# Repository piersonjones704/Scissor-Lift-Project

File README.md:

# Scissor Lift Project 
## Preventing scissor lift collisions on construction sites

### Overview  
This project, developed in collaboration with **Skanska**, aims to reduce jobsite accidents by integrating a **low-cost collision detection and avoidance system** into industrial scissor lifts.  

---

### Team  
- **Team Members:** Pierson Jones, Parker Jones, Jack Oakman, Aaryan Nanekar 
- **Project Lead:** Pierson Jones
- **Mechatronics Team Lead:** Parker Jones 
- **Client Partner:** Skanska USA

---

### License  
This project is currently **private and under client collaboration**. Portions may be shared publicly for academic or demonstration purposes only.

---

### Acknowledgements  
Special thanks to **Skanska, Duke University’s EGR101 & EGR102 Course, Dr. Glass, and Shane Trent** for mentorship, technical guidance, and access to testing and prototyping facilities.

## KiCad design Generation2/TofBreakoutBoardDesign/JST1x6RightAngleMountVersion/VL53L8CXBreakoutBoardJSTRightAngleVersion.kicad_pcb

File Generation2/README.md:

# Scissor Lift Collision Prevention Module
## Generation 2 - Time of Flight Sensors

### Overview  
This project, developed in collaboration with **Skanska**, aims to reduce jobsite accidents by integrating a **low-cost collision detection and avoidance system** into industrial scissor lifts.  

Generation 2 is a work in progress. The goal is to replace Generation 1's single mechanically-swept ultrasonic module with a static array of  6 VL53L8CX time-of-flight sensors, each mounted at a different fixed angle around the lift — eliminating the need for a servo sweep entirely. 

This semester, single-sensor operation was validated end-to-end, including adaptive ranging and a power-optimized configuration. Reliably running all 6 sensors on a shared I2C bus has been achieved. To complete this generation, combining all 6 sensors, with the buzzer and hysteresis logic, is next.

---

### Key Features  
**Validated (single sensor):**
- **2 Axes of Detection:** 6 VL53L8CX time of flight sensor readings for reliable distance measurement under varying noise and lighting conditions for 90° vertical and 135° horizontal per module.
- **Adaptive Ranging:** Frequency scales between **1 Hz (idle/far range)** and **6 Hz (near-range detection)** based on the closest detected object, with hysteresis (2 consecutive near readings to speed up; object gone 4+ seconds and 2 consecutive far readings to slow back down). Resolution held fixed at 4×4 to avoid the heavier reconfiguration cost of a resolution switch.
- **Smoothed Buzzer Alerts:** Proximity-based beep profiles that step one level at a time rather than jumping directly to a target profile.
- **Structured Power Optimization:** Configuration changes (ranging frequency, resolution, integration time, ranging mode, ESP32 light sleep with INT-pin wake, VHV recalibration interval) were tested one variable at a time (Tests 1–17) against a shared baseline, with current logged at each step to guide the final single-sensor configuration. Key findings: autonomous mode draws short bursts (~42–45 mA at 8×8, ~16 mA at 4×4) versus a sustained ~66 mA in continuous mode, and ESP32 light sleep reduced system draw from ~50 mA to ~11 mA (USB attached, like-for-like). In a 30-minute bench-supply comparison (no USB, 20% object-detected weighting), the estimated 10-hour energy use of the single-sensor module fell from ~480 mAh (baseline) to ~19 mAh (optimized), a ~96% reduction. Limitations: sub-milliamp averages were calculated from duty cycle rather than measured directly because multimeter sampling cannot resolve short bursts; the baseline was measured on USB power and the optimized run on a bench supply; and Wi-Fi and hardware-shutdown (LPn) power effects were not tested. Full 6-sensor array power has not yet been characterized.

**Validated (multi-sensor, in progress toward full 6-sensor array):**
- **Multi-Sensor I2C Addressing:** Multi-Sensor I2C Addressing: A hardware I2C multiplexer (TCA9548A/PCA9548A) successfully addresses all 6 VL53L8CX sensors simultaneously, each mounted at its intended final angle. Channel-to-angle mapping (each sensor's mountYawDeg/mountPitchDeg in firmware) has been verified against physical sensor position, not just assumed. An earlier unreliable version of multi-sensor addressing was root-caused to an intermittent short between adjacent breadboard pull-up resistor leads. This was not an addressing or firmware issue. Additionally, it is important to note that channel 4 on the MUX is not working and consistently causes channel 3 and onwards to fail. Thus, sensor 5 is being put on channel 5. A separate software-assigned addressing approach (sequenced LPn/shutdown pin control, no physical mux) was also attempted and has not yet been made reliable.
- **Per-Zone Sub-Angle Correction:** Each sensor's 4×4 zone grid is used to refine object direction beyond the sensor's overall mounting angle. The VL53L8CX's zone-to-real-world mapping was empirically determined (not assumed from documentation alone, which describes an internal lens flip but not how it interacts with this board's physical mounting) via three independent tests: a four-corner sweep, a column-order sweep, and a dead-center object test. All three confirmed the same mapping, giving validated 3D (x/y/z) lift-relative object positioning per sensor rather than a single flat distance value.
    - Currently two simplifications are made about how the current coordinate model is treated:
    1. All 6 sensors are assumed to be sharing one physical origin point. This does not account for their 1-2cm spread on the mounting plates.
    2. Yaw/pitch rotations are additively combined rather than using full rotation matrices. 
    - The current use-case of this product allows for these to be made. They will be reconsidered after real situational testing on the construction site.
- **Zone Selection Hysteresis:** Zone slection hysteresis was added for improved stability between x, y, and z readings from each sensor. If a stationary object is near the boundary of two zones within one sensor's grid, then there may be flickering between readings causing the angle/z axis to change even though the object is stationary. This addition requires two consecutive readings before it replaces the zone that is detecting the closest object.

**Client Collaboration:** Developed through Duke's EGR102 course; presented deliverables to Skanska and collaborated to meet client specifications - as part of **client focused development**. Also coordinated with a power consultant on different strategies to optimize the system's power consumption, aiming to reach industry grade efficiency and reliability.

---

### System Architecture
**Target has been validated:** VL53L8CX x6 (via I2C mux), ESP32-S3, Piezo Buzzer

---

### Technical Stack  
- **Hardware:** VL53L8CX (6 validated simultaneously), ESP32-S3-DevKitC-1 (WROOM-2), TCA9548A/PCA9548A I2C multiplexer (6-sensor operation validated), piezo buzzer, transistor driver  
- **Software:** Arduino IDE (C/C++), with ST's VL53L8CX ULD API, VSCode, Python + PyGame (single-sensor visualizer used during bring-up).
- **Documentation:** Structured power-characterization test tables (Tests 1–11).

---

### Code
- **1TOFSensorModule_PerformanceCode.ino -** Most up-to-date firmware for this generation. Single VL53L8CX sensor running adaptive 1/6 Hz ranging at fixed 4×4 resolution with hysteresis-based mode switching and smoothed buzzer transitions. Written as a validated single-sensor building block, with the architecture intended to scale to 6 sensors once testing with the MUX has been completed.
- **Test1_Default_Baseline.ino, Test2_FrequencySweep.ino, plus Test files 3-11, power_test_common_h.ino -** Isolated power-characterization test sketches, each varying a single parameter (ranging frequency, resolution, integration time, ranging mode, sensor power/sleep state, duty cycling, VHV repeat count) against a shared baseline defined in **power_test_common.h**. Used to build the current-draw comparison tables that informed the configuration in **1TOFSensorModule_PerformanceCode.ino**.
- **MUX_TestCode.ino -** TCA9548A/PCA9548A-style I2C channel multiplexing test code. Validated for reliable 6-sensor addressing across repeated resets; next step is polling each sensor to achieve distance data from individual sensors.
- **SoftwareassigningI2CSensors.ino -** In-progress alternate approach assigning individual I2C addresses to each VL53L8CX sensor via sequenced LPn pin control, instead of a physical multiplexer.

---

### Alternate Approaches Considered
Before settling on the static 6-sensor array, a mechanically-swept single-sensor design was also prototyped. This used a single VL53L7CX 8×8-zone sensor mounted on a 270° servo, sweeping the corner similarly in spirit to Generation 1's dual-ultrasonic servo approach. This exploration included trigonometric threshold scaling to correct for edge angles, self-masking to filter out the lift's own mounting structure, and an adaptive fast/slow sweep rate with hysteresis. It was set aside in favor of the static multi-sensor array that reduced power consumption and avoided the added mechanical complexity, wear, and single point of failure of a servo.Additionally, full simultaneous coverage from fixed sensors will promote accuracy and efficiency once the I2C address issues are resolved.

---

### Results  
- Single-sensor adaptive ranging and power-optimized configuration validated.
- Structured, single-variable power characterization (Tests 1–11) completed — reduced single-sensor average current draw ~83% (from an estimated ~500 mA baseline to 86 mA).
- 6-sensor I2C multiplexer addressing validated as stable across 5+ consecutive resets, after root-causing an earlier intermittent failure to a breadboard pull-up resistor short (not an addressing/firmware issue). IMPORTANT: channel 4 on mux causes consistent failing. For sensor 5 use channel 5 instead of channel 4 and for sensor 6 use channel 6.
- Full 6-sensor channel-to-angle mapping validated: running MultiSensorAngleCalibration.ino, placing an object close to one sensor at a time confirmed each channel's serial output matches its physical position — e.g. an object 100mm from the top-left sensor showed the Top-Left channel reporting ~100mm while all other channels reported no nearby object. This confirms the coordinate transform's angle table is correct, not just assumed.- I2C/Serial Re-Init Crash: Initializing all 6 sensors in a loop originally caused a Guru Meditation Error (null-pointer panic, PC: 0x00000000) partway through setup. Root cause: sensor_init() called Wire.begin() and Serial.begin() on every invocation (once per sensor), and repeatedly re-initializing the ESP32's I2C driver mid-program corrupted its internal state. Fixed by guarding both calls with a static bool flag in power_test_common.h so the I2C and Serial peripherals are only truly initialized once, on the first sensor, regardless of how many times sensor_init() is called.
- Zone-level angle correction validated via three independent physical tests on the Top-Middle sensor (corner sweep, column sweep, dead-center object), all consistent with each other. This confirmed that the sensor's true zone-to-direction mapping differs from the datasheet-derived assumption due to this board's physical mounting rotation.

---

### Next Steps
1. Characterize power consumption with 6 sensors.
2. Integrate the piezo buzzer and hysteresis logic with the multiplexed 6 sensors. 
3. Start planning and developing the PCB design to consolidate the product's footprint
4. Re-run power characterization on the full array with staggered polling.
5. Obtain system-level results (Coverage, blind-spot reduction, per-unit cost, ROI, etc.)

---

### Team  
- **Project Leads:** Pierson Jones, Parker Jones, Jack Oakman, Aaryan Nanekar  
- **Client Partner:** Skanska USA

---

### License  
This project is currently **private and under client collaboration**. Portions may be shared publicly for academic or demonstration purposes only.

---

### Acknowledgements  
Special thanks to **Skanska, Duke University’s EGR102 Course, Dr. Glass, and Shane Trent** for mentorship, technical guidance, and access to testing and prototyping facilities.

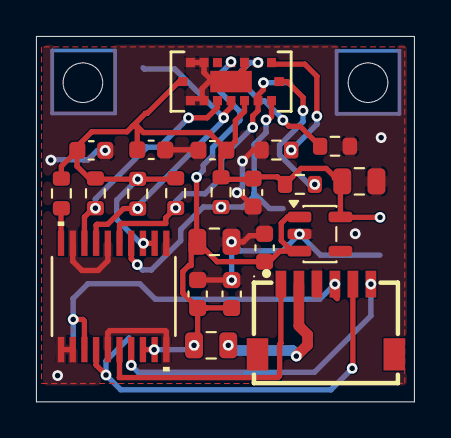
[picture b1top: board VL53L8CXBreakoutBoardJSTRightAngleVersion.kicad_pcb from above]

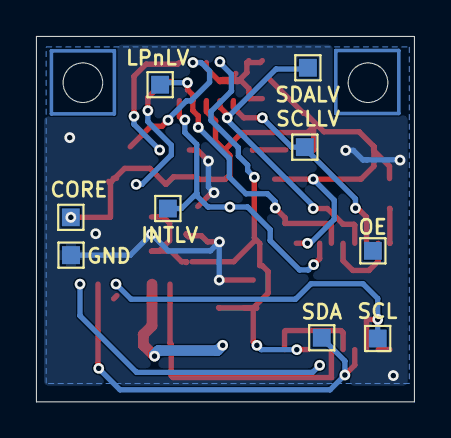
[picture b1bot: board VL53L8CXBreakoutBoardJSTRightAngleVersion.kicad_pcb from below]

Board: 2 copper layers, 21.0 x 20.3 mm, 33 parts (9 on the bottom side), 16 nets.

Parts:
C1: 1µF; C_0603_1608Metric
C2, C3, C5, C6, C7, C8: 0.1µF; C_0603_1608Metric
C4, C9: 4.7µF; C_0805_2012Metric
C10: 10µF; C_0805_2012Metric
CN2: Right Angle Locking Connector; CONN-SMD_6P-P1.00_5015680607
CORE: TestPoint; TestPoint_Pad_1.0x1.0mm
GND: TestPoint; TestPoint_Pad_1.0x1.0mm
H1, H2: MountingHole; MountingHole_2.2mm_M2
INTLV: TestPoint; TestPoint_Pad_1.0x1.0mm
LPnLV: TestPoint; TestPoint_Pad_1.0x1.0mm
OE: TestPoint; TestPoint_Pad_1.0x1.0mm
R1: 10k; R_0603_1608Metric
R2, R3: 2.2k; R_0603_1608Metric
R4, R5, R6, R7, R8: 47k; R_0603_1608Metric
SCL: TestPoint; TestPoint_Pad_1.0x1.0mm
SCLLV: TestPoint; TestPoint_Pad_1.0x1.0mm
SDA: TestPoint; TestPoint_Pad_1.0x1.0mm
SDALV: TestPoint; TestPoint_Pad_1.0x1.0mm
U1: VL53L8CX
U2: NXS0108
U3: AP2112K-1.8; SOT-23-5

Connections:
/INT: CN2.6, U2.17 (B3)
/INTLV: INTLV.1 (1_1), R6.2, U1.A1 (INT), U2.4 (A3)
/LPn: CN2.1, U2.16 (B4)
/LPnLV: LPnLV.1 (1_1), R5.2, U1.A2 (LPN), U2.5 (A4)
/SCL: CN2.4, SCL.1 (1_1), U2.13 (B7)
/SCLLV: R2.2, SCLLV.1 (1_1), U1.A5 (SCL/MCLK), U2.8 (A7)
/SDA: CN2.5, SDA.1 (1_1), U2.14 (B6)
/SDALV: R3.2, SDALV.1 (1_1), U1.A4 (SDA/MOSI), U2.7 (A6)
CORE/IOVDD: C3.1, C4.1, C5.2, C7.2, C8.1, CORE.1 (1_1), R1.1, R2.1, R3.1, R4.1, R5.1, R6.1, U1.A3 (IOVDD), U1.B7 (CORE_1V8), U2.2 (VCC(A)), U2.3 (A2), U3.5 (VOUT)
GND: C1.2, C2.2, C3.2, C4.2, C5.1, C6.2, C7.1, C8.2, C9.2, CN2.3, GND.1 (1_1), R7.2, R8.2, U1.A6 (RSVD1), U1.A7 (RSVD2), U1.B4 (THERMALPAD), U1.C3 (GND), U1.C6 (RSVD3), U1.C7 (GROUND), U2.1 (A1), U2.6 (A5), U2.9 (A8), U2.11 (GND), U2.12 (B8), U2.15 (B5), U2.20 (B1), U3.2 (GND)
unnamed: C10.2, CN2.2
unnamed: R8.1, U1.C2 (NCS)
unnamed: R7.1, U1.C1 (SPI_I2C_N)
unnamed: R4.2, U1.B1 (SYNC)
unnamed: R1.2, U2.10 (OE)
VIN: C1.1, C2.1, C6.1, C9.1, C10.1, U1.C4 (AVDD), U2.18 (B2), U2.19 (VCC(B)), U3.1 (VIN), U3.3 (EN)

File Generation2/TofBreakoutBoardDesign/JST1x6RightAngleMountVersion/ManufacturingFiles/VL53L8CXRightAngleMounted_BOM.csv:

"Reference","Value","Datasheet","Footprint","Qty","LCSC Part","Manufacturer"
"C1","1µF","https://jlc-prod-smt.oss-eu-central-1.aliyuncs.com/smtDataMa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","Capacitor_SMD:C_0603_1608Metric","1","C1592","Samsung Electro-Mechanics"
"C2,C3,C5,C6,C7,C8","0.1µF","https://jlc-prod-smt.oss-eu-central-1.aliyuncs.com/smtDataMa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","Capacitor_SMD:C_0603_1608Metric","6","C1591","Samsung Electro-Mechanics"
"C4,C9","4.7µF","https://jlc-prod-smt.oss-eu-central-1.aliyuncs.com/smtDataMa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","Capacitor_SMD:C_0805_2012Metric","2","C1746","Samsung Electro-Mechanics"
"C10","10µF","https://jlc-prod-smt.oss-eu-central-1.aliyuncs.com/smtDataMa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","Capacitor_SMD:C_0805_2012Metric","1","C15850","Samsung Electro-Mechanics"
"CN2","Right Angle Locking Connector","https://www.lcsc.com/datasheet/C505000.pdf","JLCPCB_Library:CONN-SMD_6P-P1.00_5015680607","1","C505000","MOLEX"
"CORE1,GND1,INTLV1,LPnLV1,OE1,SCL1,SCLLV1,SDA1,SDALV1","TestPoint","","TestPoint:TestPoint_Pad_1.0x1.0mm","9","C9900119237","JLCPCB Assembly"
"R1","10k","https://jlc-prod-smt.oss-eu-central-1.aliyuncs.com/smtDataMa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","Resistor_SMD:R_0603_1608Metric","1","C15401","UNI-ROYAL(Uniroyal Elec)"
"R2,R3","2.2k","https://jlc-prod-smt.oss-eu-central-1.aliyuncs.com/smtDataMa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","Resistor_SMD:R_0603_1608Metric","2","C4190","UNI-ROYAL(Uniroyal Elec)"
"R4,R5,R6,R7,R8","47k","https://jlc-prod-smt.oss-eu-central-1.aliyuncs.com/smtDataMa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","Resistor_SMD:R_0603_1608Metric","5","C25600","UNI-ROYAL(Uniroyal Elec)"
"U1","VL53L8CX","https://www.st.com/resource/en/datasheet/vl53l8cx.pdf","VL53L8CX:VL53L8CX","1","C7386355","STMicroelectronics"
"U2","NXS0108","https://jlc-prod-smt.oss-eu-central-1.aliyuncs.com/smtDataMa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","NXS0108:NXS0108","1","C4364113","Nexperia"
"U3","AP2112K-1.8","https://www.diodes.com/assets/Datasheets/AP2112.pdf","Package_TO_SOT_SMD:SOT-23-5","1","C176944","Diodes Incorporated"

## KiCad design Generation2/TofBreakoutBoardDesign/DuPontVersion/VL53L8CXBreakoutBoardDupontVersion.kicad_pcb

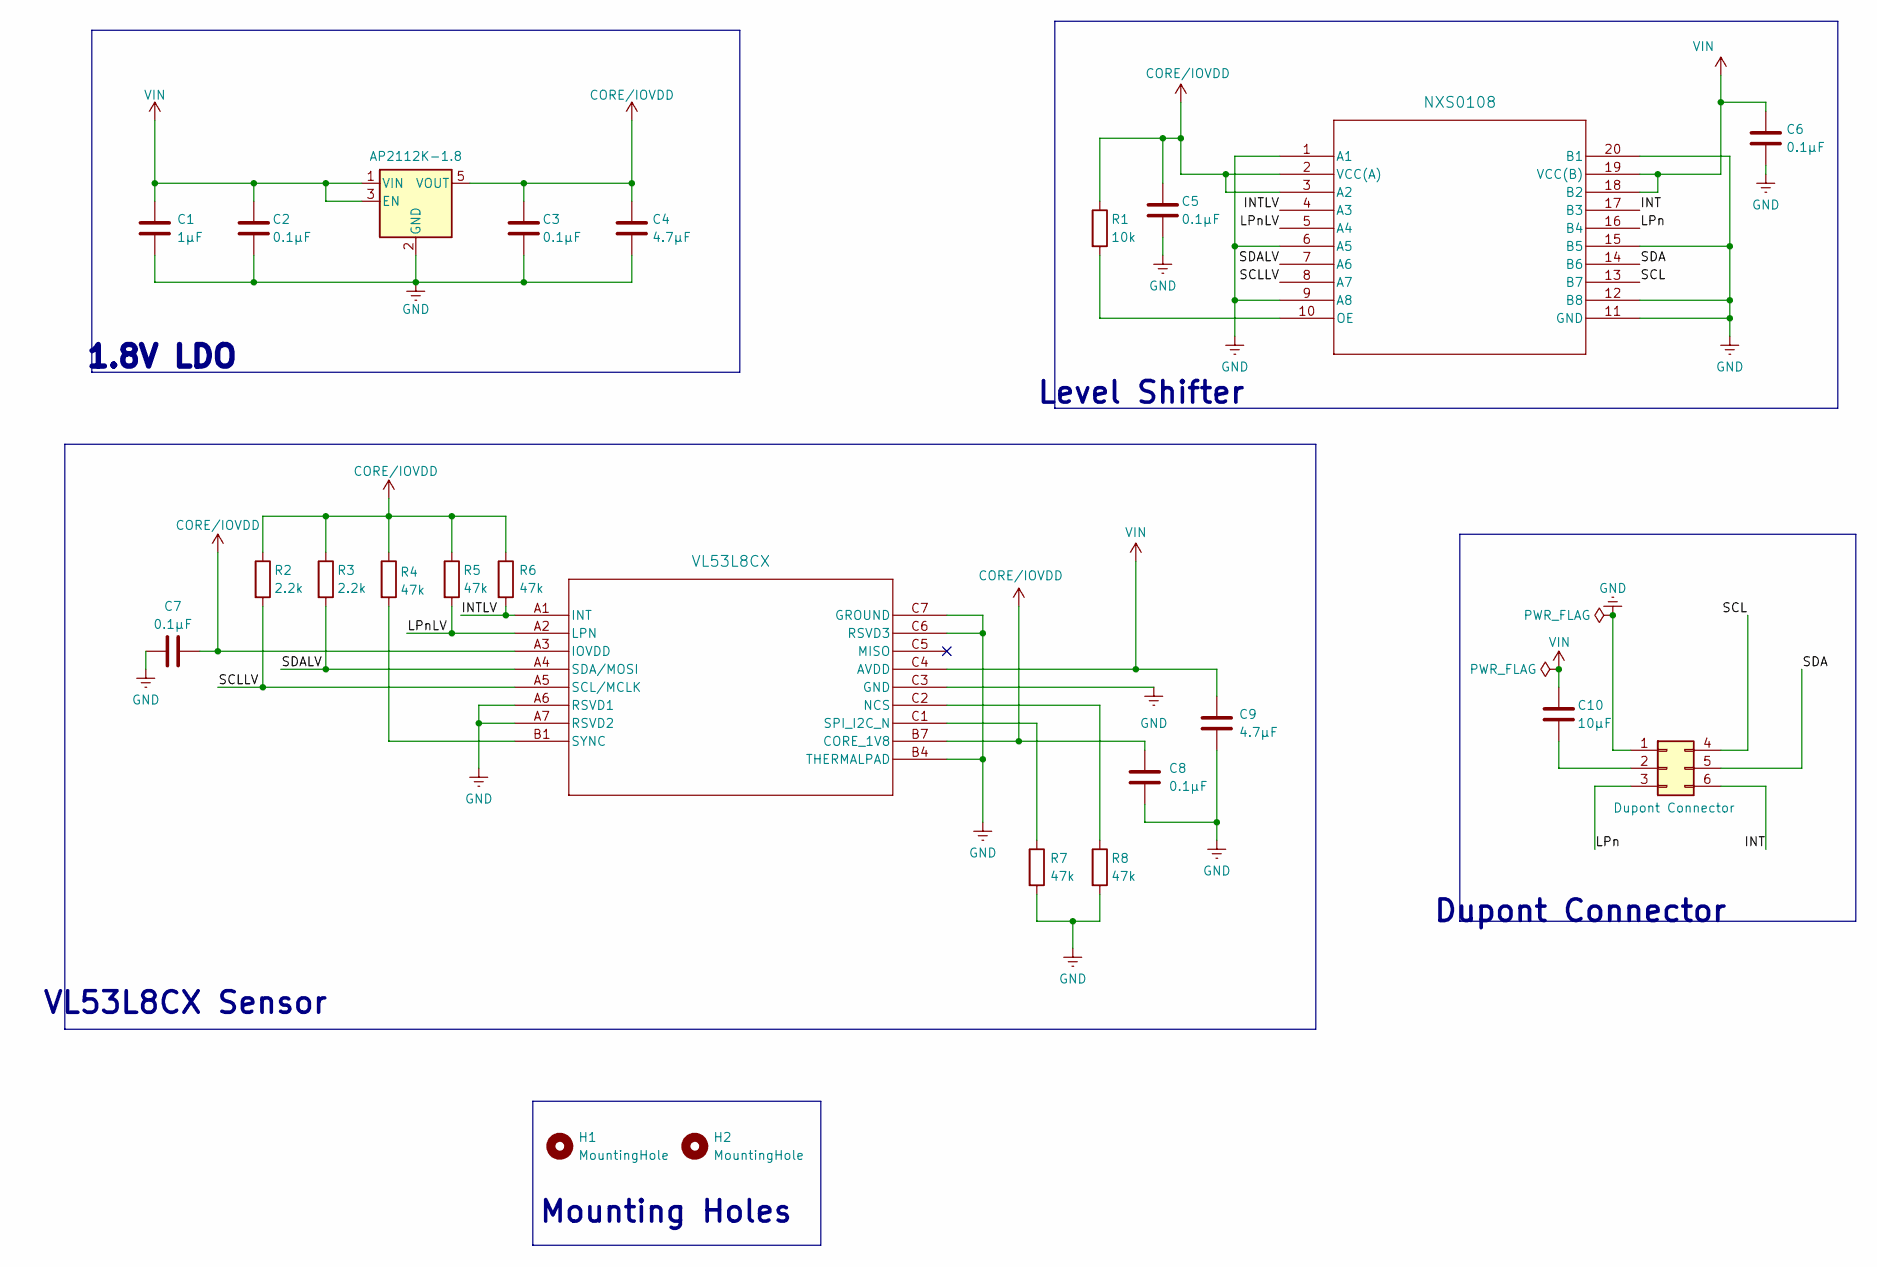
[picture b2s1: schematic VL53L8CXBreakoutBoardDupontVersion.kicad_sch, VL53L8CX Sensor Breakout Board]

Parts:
C1: 1µF; C_0603_1608Metric
C2, C3, C5, C6, C7, C8: 0.1µF; C_0603_1608Metric
C4, C9: 4.7µF; C_0805_2012Metric
C10: 10µF; C_0805_2012Metric
H1, H2: MountingHole; MountingHole_2.2mm_M2_Pad_TopBottom
J1: Dupont Connector; PinHeader_2x03_P2.00mm_Vertical
R1: 10k; R_0603_1608Metric
R2, R3: 2.2k; R_0603_1608Metric
R4, R5, R6, R7, R8: 47k; R_0603_1608Metric
U1: VL53L8CX
U2: NXS0108
U3: AP2112K-1.8; SOT-23-5

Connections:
/INT: J1.6, U2.17 (B3)
/INTLV: R6.2, U1.A1 (INT), U2.4 (A3)
/LPn: J1.3, U2.16 (B4)
/LPnLV: R5.2, U1.A2 (LPN), U2.5 (A4)
/SCL: J1.4, U2.13 (B7)
/SCLLV: R2.2, U1.A5 (SCL/MCLK), U2.8 (A7)
/SDA: J1.5, U2.14 (B6)
/SDALV: R3.2, U1.A4 (SDA/MOSI), U2.7 (A6)
CORE/IOVDD: C3.1, C4.1, C5.2, C7.2, C8.1, R1.1, R2.1, R3.1, R4.1, R5.1, R6.1, U1.A3 (IOVDD), U1.B7 (CORE_1V8), U2.2 (VCC(A)), U2.3 (A2), U3.5 (VOUT)
GND: C1.2, C2.2, C3.2, C4.2, C5.1, C6.2, C7.1, C8.2, C9.2, J1.1, R7.2, R8.2, U1.A6 (RSVD1), U1.A7 (RSVD2), U1.B4 (THERMALPAD), U1.C3 (GND), U1.C6 (RSVD3), U1.C7 (GROUND), U2.1 (A1), U2.6 (A5), U2.9 (A8), U2.11 (GND), U2.12 (B8), U2.15 (B5), U2.20 (B1), U3.2 (GND)
unnamed: C10.2, J1.2
unnamed: R8.1, U1.C2 (NCS)
unnamed: R7.1, U1.C1 (SPI_I2C_N)
unnamed: R4.2, U1.B1 (SYNC)
unnamed: R1.2, U2.10 (OE)
VIN: C1.1, C2.1, C6.1, C9.1, C10.1, U1.C4 (AVDD), U2.18 (B2), U2.19 (VCC(B)), U3.1 (VIN), U3.3 (EN)

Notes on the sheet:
Mounting Holes
Level Shifter
Dupont Connector
VL53L8CX Sensor
1.8V LDO

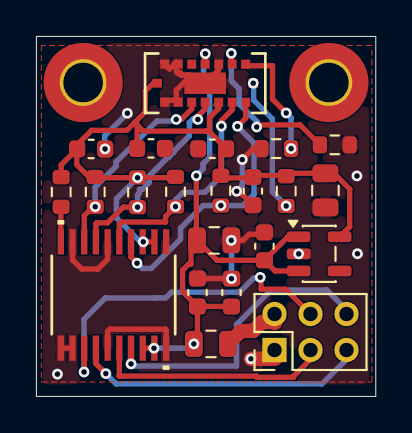
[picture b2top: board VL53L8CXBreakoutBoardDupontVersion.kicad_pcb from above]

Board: 2 copper layers, 18.8 x 20.0 mm, 24 parts (0 on the bottom side), 16 nets.
